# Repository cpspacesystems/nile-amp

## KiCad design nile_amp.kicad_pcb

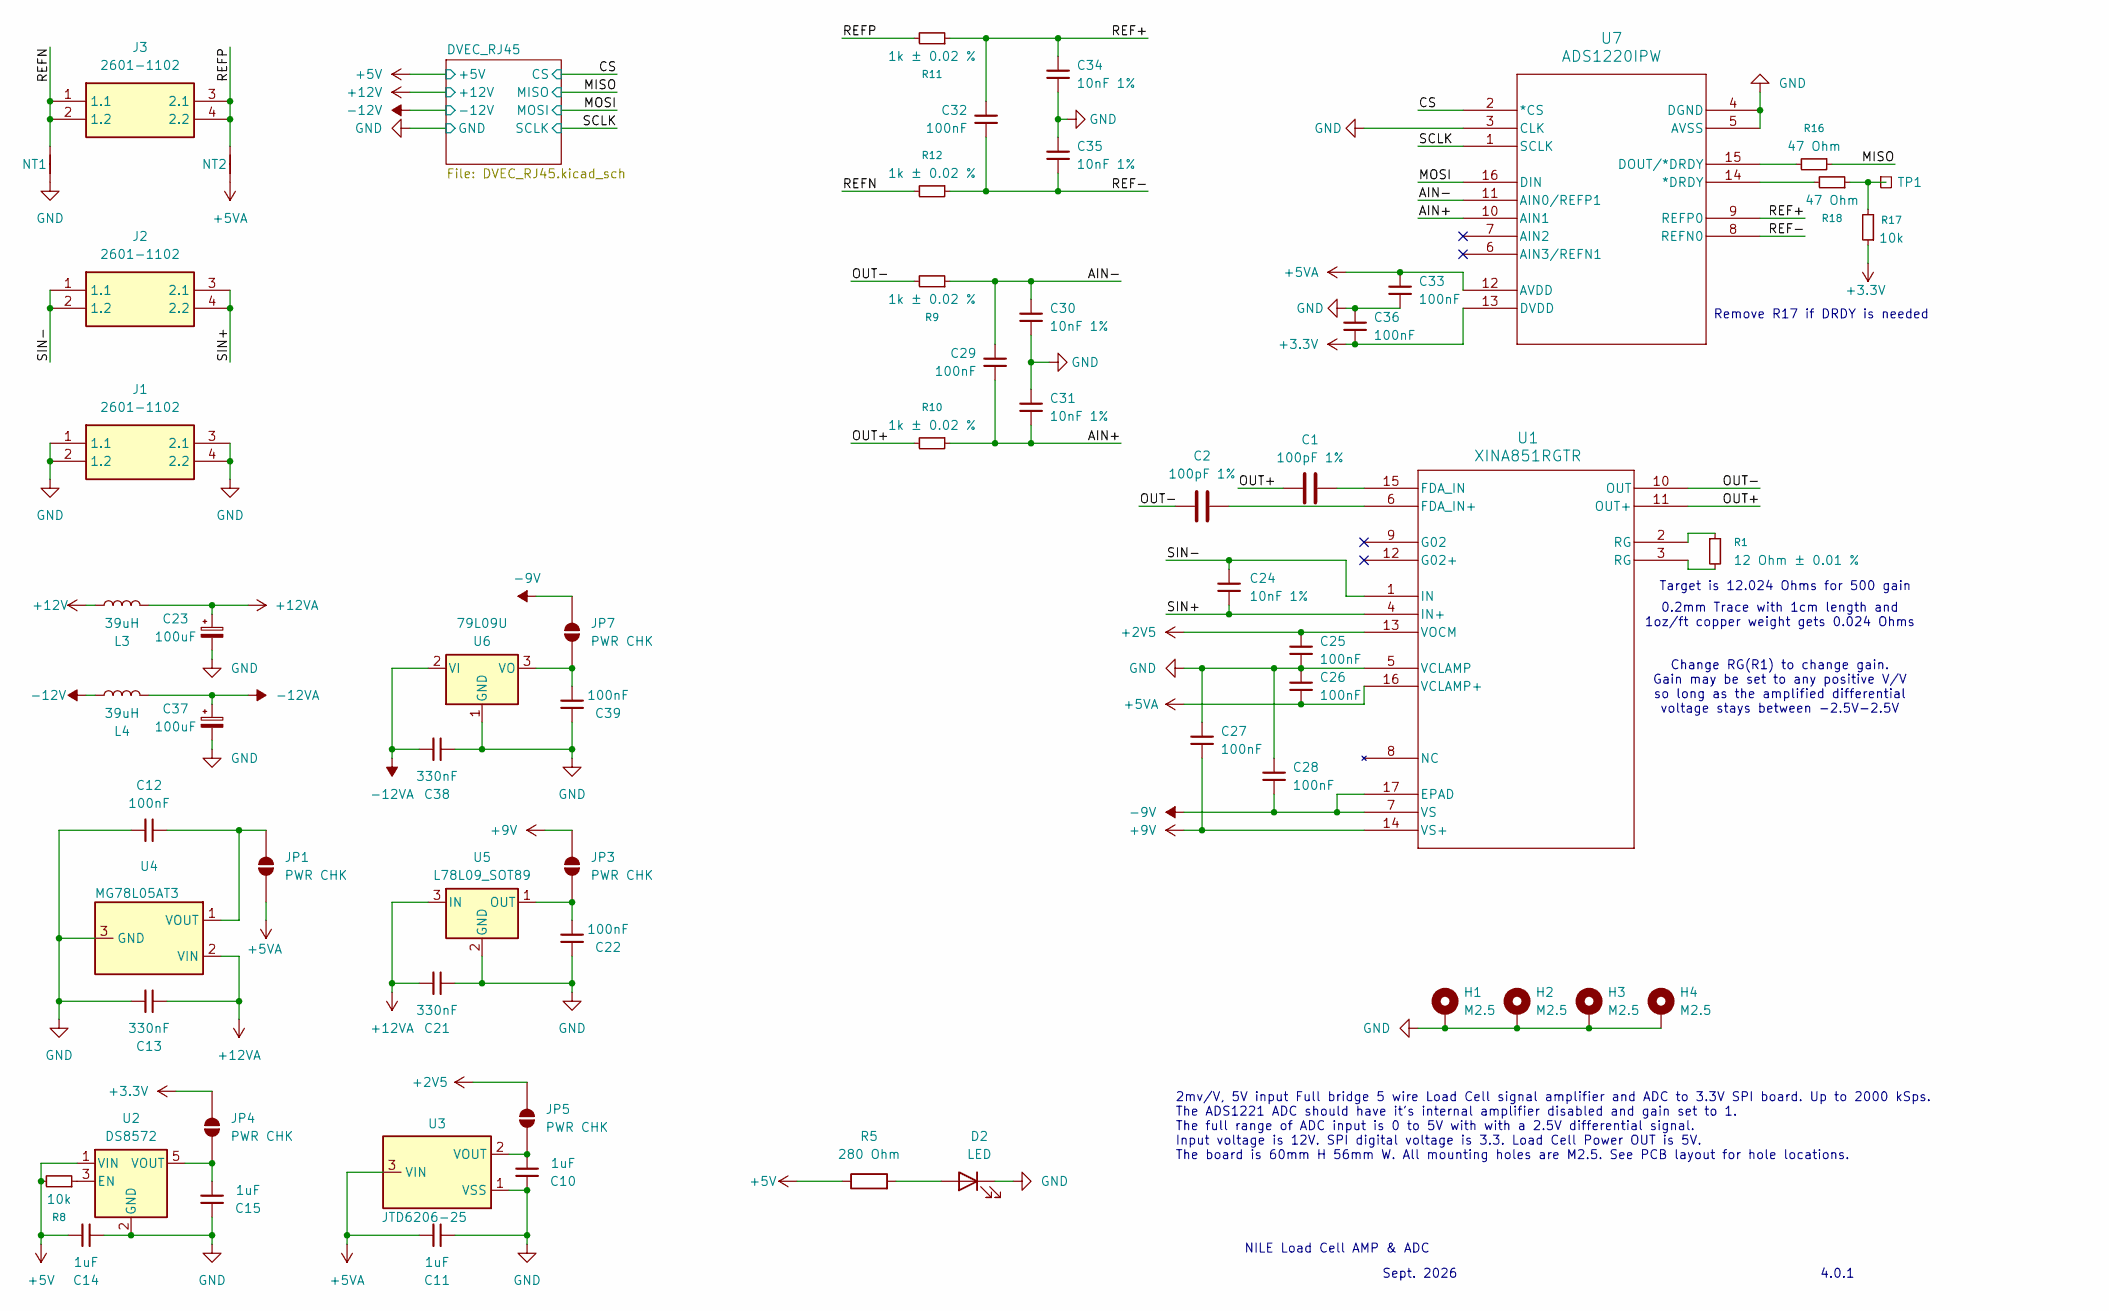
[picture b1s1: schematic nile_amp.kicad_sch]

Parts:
C1, C2: 100pF 1%; C_0201_0603Metric
C10, C11, C14, C15: 1uF; C_0402_1005Metric
C12, C22, C25, C26, C27, C28, C29, C32, C33, C36, C39: 100nF; C_0402_1005Metric
C13, C21, C38: 330nF; C_0603_1608Metric
C23, C37: 100uF; CP_Radial_D5.0mm_P2.00mm
C24, C30, C31, C34, C35: 10nF 1%; C_0603_1608Metric
D2: LED; LED_0603_1608Metric_Pad1.05x0.95mm_HandSolder
H1, H2, H3, H4: M2.5; MountingHole_2.5mm_Pad_TopBottom
J1, J2, J3: 2601-1102; 26011102; Manufacturer_Part_Number 2601-1102
JP1, JP3, JP4, JP5, JP7: PWR CHK; C_0201_0603Metric
L3, L4: 39uH; CMLF0504-390KTT
NT1, NT2: NetTie_2; NetTie-2_SMD_Pad0.5mm
R1: 12 Ohm ± 0.01 %; R_0805_2012Metric
R5: 280 Ohm; R_0402_1005Metric_Pad0.72x0.64mm_HandSolder
R8, R17: 10k; R_0402_1005Metric_Pad0.72x0.64mm_HandSolder
R9, R10, R11, R12: 1k ± 0.02 %; R_0603_1608Metric
R16, R18: 47 Ohm; R_0402_1005Metric_Pad0.72x0.64mm_HandSolder
TP1: TestPoint_Square; TestPoint_Pad_2.5x2.5mm
U1: XINA851RGTR; VQFN16_RGT_TEX
U2: DS8572; SOT-23-5
U3: JTD6206-25; SOT-23
U4: MG78L05AT3; SOT-23-3
U5: L78L09_SOT89; SOT-89-3
U6: 79L09U; SOT-89-3
U7: ADS1220IPW; PW16

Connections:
+2V5: C25.1, JP5.1 (A), U1.13 (VOCM)
+3.3V: C36.2, JP4.1 (A), R17.1, U7.13 (DVDD)
+5V: C14.1, R5.1, R8.2, U2.1 (VIN); also elsewhere on the board
+5VA: C11.1, C26.2, C33.1, JP1.2 (B), NT2.1, U1.16 (VCLAMP+), U3.3 (VIN), U7.12 (AVDD)
+9V: C27.2, JP3.1 (A), U1.14 (VS+)
+12V: L3.2; also elsewhere on the board
+12VA: C13.2, C21.2, C23.1, L3.1, U4.2 (VIN), U5.3 (IN)
-9V: C28.2, JP7.1 (A), U1.7 (VS), U1.17 (EPAD)
-12V: L4.2; also elsewhere on the board
-12VA: C37.1, C38.2, L4.1, U6.2 (VI)
/AIN+: C29.2, C31.2, R10.1, U7.10 (AIN1)
/AIN-: C29.1, C30.1, R9.1, U7.11 (AIN0/REFP1)
/CS: U7.2 (*CS); also elsewhere on the board
/MISO: R16.1; also elsewhere on the board
/MOSI: U7.16 (DIN); also elsewhere on the board
/OUT+: C1.1, R10.2, U1.11 (OUT+)
/OUT-: C2.1, R9.2, U1.10 (OUT)
/REF+: C32.1, C34.1, R11.1, U7.9 (REFP0)
/REF-: C32.2, C35.2, R12.1, U7.8 (REFN0)
/REFN: J3.1 (1.1), J3.2 (1.2), NT1.2, R12.2
/REFP: J3.3 (2.1), J3.4 (2.2), NT2.2, R11.2
/SCLK: U7.1 (SCLK); also elsewhere on the board
/SIN+: C24.2, J2.3 (2.1), J2.4 (2.2), U1.4 (IN+)
/SIN-: C24.1, J2.1 (1.1), J2.2 (1.2), U1.1 (IN)
GND: C10.1, C11.2, C12.2, C13.1, C14.2, C15.1, C21.1, C22.1, C23.2, C25.2, C26.1, C27.1, C28.1, C30.2, C31.1, C33.2, C34.2, C35.1, C36.1, C37.2, C38.1, C39.1, D2.1 (K), H1.1 (1_1), H2.1 (1_1), H3.1 (1_1), H4.1 (1_1), J1.1 (1.1), J1.2 (1.2), J1.3 (2.1), J1.4 (2.2), NT1.1, U1.5 (VCLAMP), U2.2 (GND), U3.1 (VSS), U4.3 (GND), U5.2 (GND), U6.1 (GND), U7.3 (CLK), U7.4 (DGND), U7.5 (AVSS); also elsewhere on the board
unnamed: D2.2 (A), R5.2
unnamed: C12.1, JP1.1 (A), U4.1 (VOUT)
unnamed: C22.2, JP3.2 (B), U5.1 (OUT)
unnamed: C15.2, JP4.2 (B), U2.5 (VOUT)
unnamed: C10.2, JP5.2 (B), U3.2 (VOUT)
unnamed: C39.2, JP7.2 (B), U6.3 (VO)
unnamed: R1.1, U1.2 (RG)
unnamed: R1.2, U1.3 (RG)
unnamed: R17.2, R18.1, TP1.1 (1_1)
unnamed: C1.2, U1.15 (FDA_IN)
unnamed: C2.2, U1.6 (FDA_IN+)
unnamed: R8.1, U2.3 (EN)
unnamed: R18.2, U7.14 (*DRDY)
unnamed: R16.2, U7.15 (DOUT/*DRDY)

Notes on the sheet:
4.0.1
Remove R17 if DRDY is needed
NILE Load Cell AMP & ADC
Target is 12.024 Ohms for 500 gain
2mv/V, 5V input Full bridge 5 wire Load Cell signal amplifier and ADC to 3.3V SPI board. Up to 2000 kSps. The ADS1221 ADC should have it's internal amplifier disabled and gain set to 1. The full range of ADC input is 0 to 5V with with a 2.5V differential signal. Input voltage is 12V. SPI digital vo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
Change RG(R1) to change gain. Gain may be set to any positive V/V so long as the amplified differential voltage stays between -2.5V-2.5V
0.2mm Trace with 1cm length and 1oz/ft copper weight gets 0.024 Ohms
Sept. 2026

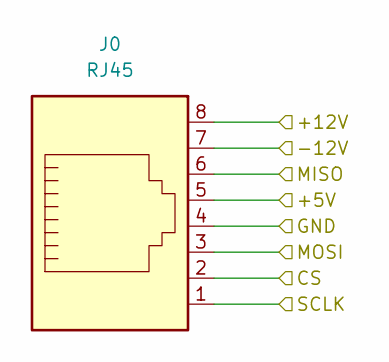
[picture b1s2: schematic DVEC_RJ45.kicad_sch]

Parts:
J0: RJ45; RJ45-TH_RJ-804-1-6 Yellow

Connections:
+5V: J0.5; also elsewhere on the board
+12V: J0.8; also elsewhere on the board
-12V: J0.7; also elsewhere on the board
/CS: J0.2; also elsewhere on the board
/MISO: J0.6; also elsewhere on the board
/MOSI: J0.3; also elsewhere on the board
/SCLK: J0.1; also elsewhere on the board
GND: J0.4; also elsewhere on the board

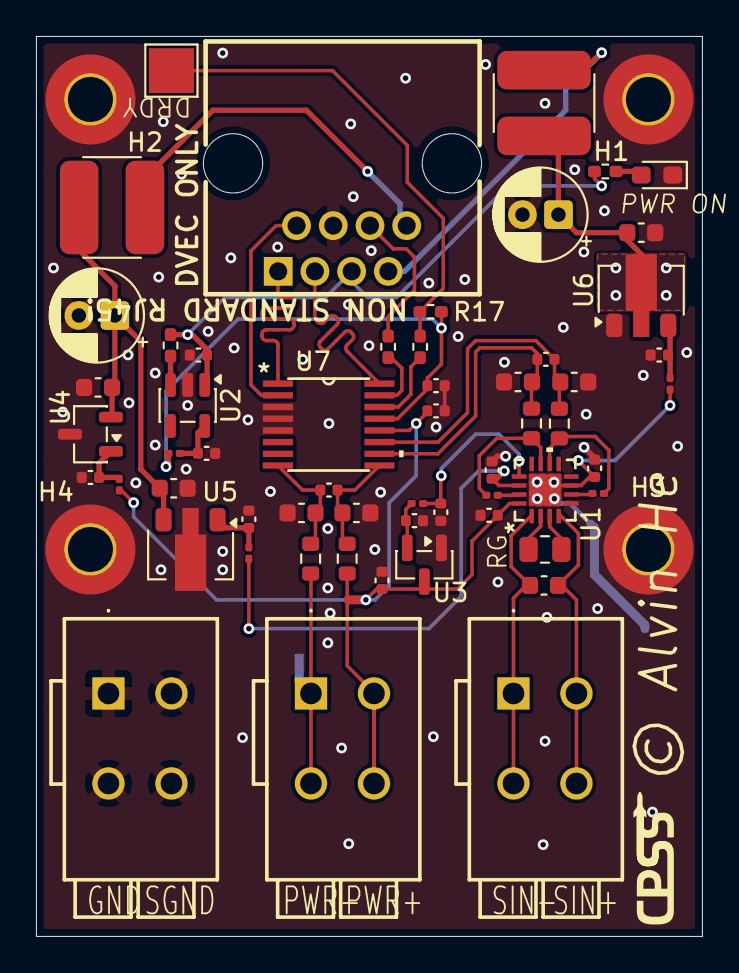
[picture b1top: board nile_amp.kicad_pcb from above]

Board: 2 copper layers, 37.0 x 50.0 mm, 63 parts (1 on the bottom side), 39 nets.

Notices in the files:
nile_amp.kicad_pcb:
© Alvin He
